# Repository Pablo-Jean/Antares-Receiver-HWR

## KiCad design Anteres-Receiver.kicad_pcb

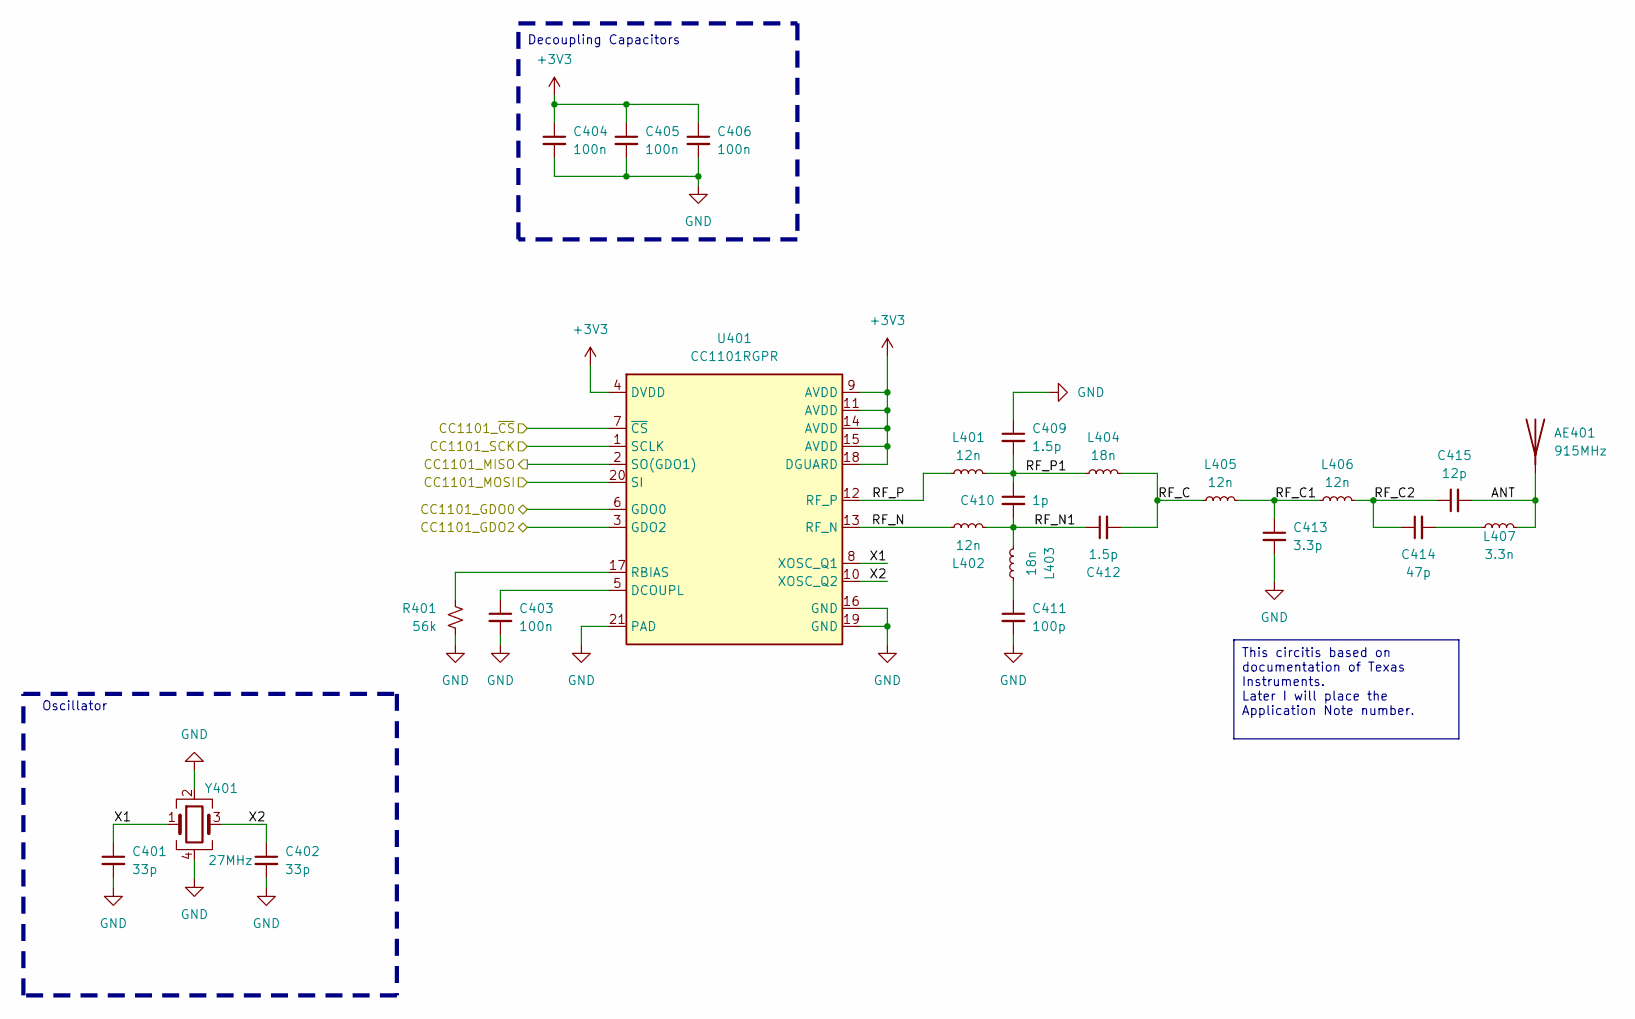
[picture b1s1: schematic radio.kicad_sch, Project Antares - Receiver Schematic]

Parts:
AE401: 915MHz; Texas_SWRA416_868MHz_915MHz
C401, C402: 33p; C_0603_1608Metric; LCSC C107047
C403, C404, C405, C406: 100n; C_0603_1608Metric; LCSC C14663
C409, C412: 1.5p; C_0603_1608Metric; LCSC C519100
C410: 1p; C_0603_1608Metric; LCSC C115062
C411: 100p; C_0603_1608Metric; LCSC C14665
C413: 3.3p; C_0603_1608Metric; LCSC C282249
C414: 47p; C_0603_1608Metric; LCSC C105622
C415: 12p; C_0603_1608Metric; LCSC C107034
L401, L402, L405, L406: 12n; L_0603_1608Metric; LCSC C75656
L403, L404: 18n; L_0603_1608Metric; LCSC C90206
L407: 3.3n; L_0603_1608Metric; LCSC C1029
R401: 56k; R_0603_1608Metric; LCSC C23206
U401: CC1101RGPR; QFN-20-1EP_4x4mm_P0.5mm_EP2.5x2.5mm_ThermalVias; LCSC C29953
Y401: 27MHz; Crystal_SMD_3225-4Pin_3.2x2.5mm; LCSC C9008

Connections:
+3V3: C404.1, C405.1, C406.1, U401.4 (DVDD), U401.9 (AVDD), U401.11 (AVDD), U401.14 (AVDD), U401.15 (AVDD), U401.18 (DGUARD); also elsewhere on the board
/MCU/CC1101_GDO0: U401.6 (GDO0); also elsewhere on the board
/MCU/CC1101_GDO2: U401.3 (GDO2); also elsewhere on the board
/MCU/CC1101_MISO: U401.2 (SO(GDO1)); also elsewhere on the board
/MCU/CC1101_MOSI: U401.20 (SI); also elsewhere on the board
/MCU/CC1101_SCK: U401.1 (SCLK); also elsewhere on the board
/MCU/CC1101_~CS: U401.7 (~CS); also elsewhere on the board
/Radio 915MHz/ANT: AE401.1 (A), C415.2, L407.2
/Radio 915MHz/RF_C: C412.2, L404.2, L405.1
/Radio 915MHz/RF_C1: C413.1, L405.2, L406.1
/Radio 915MHz/RF_C2: C414.1, C415.1, L406.2
/Radio 915MHz/RF_N: L402.1, U401.13 (RF_N)
/Radio 915MHz/RF_N1: C410.2, C412.1, L402.2, L403.2
/Radio 915MHz/RF_P: L401.1, U401.12 (RF_P)
/Radio 915MHz/RF_P1: C409.2, C410.1, L401.2, L404.1
/Radio 915MHz/X1: C401.1, U401.8 (XOSC_Q1), Y401.1
/Radio 915MHz/X2: C402.1, U401.10 (XOSC_Q2), Y401.3
GND: C401.2, C402.2, C403.2, C404.2, C405.2, C406.2, C409.1, C411.2, C413.2, R401.2, U401.16 (GND), U401.19 (GND), U401.21 (PAD), Y401.2, Y401.4; also elsewhere on the board
unnamed: C411.1, L403.1
unnamed: C414.2, L407.1
unnamed: C403.1, U401.5 (DCOUPL)
unnamed: R401.1, U401.17 (RBIAS)

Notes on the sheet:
This circitis based on documentation of Texas Instruments. Later I will place the Application Note number.
Oscillator
Decoupling Capacitors

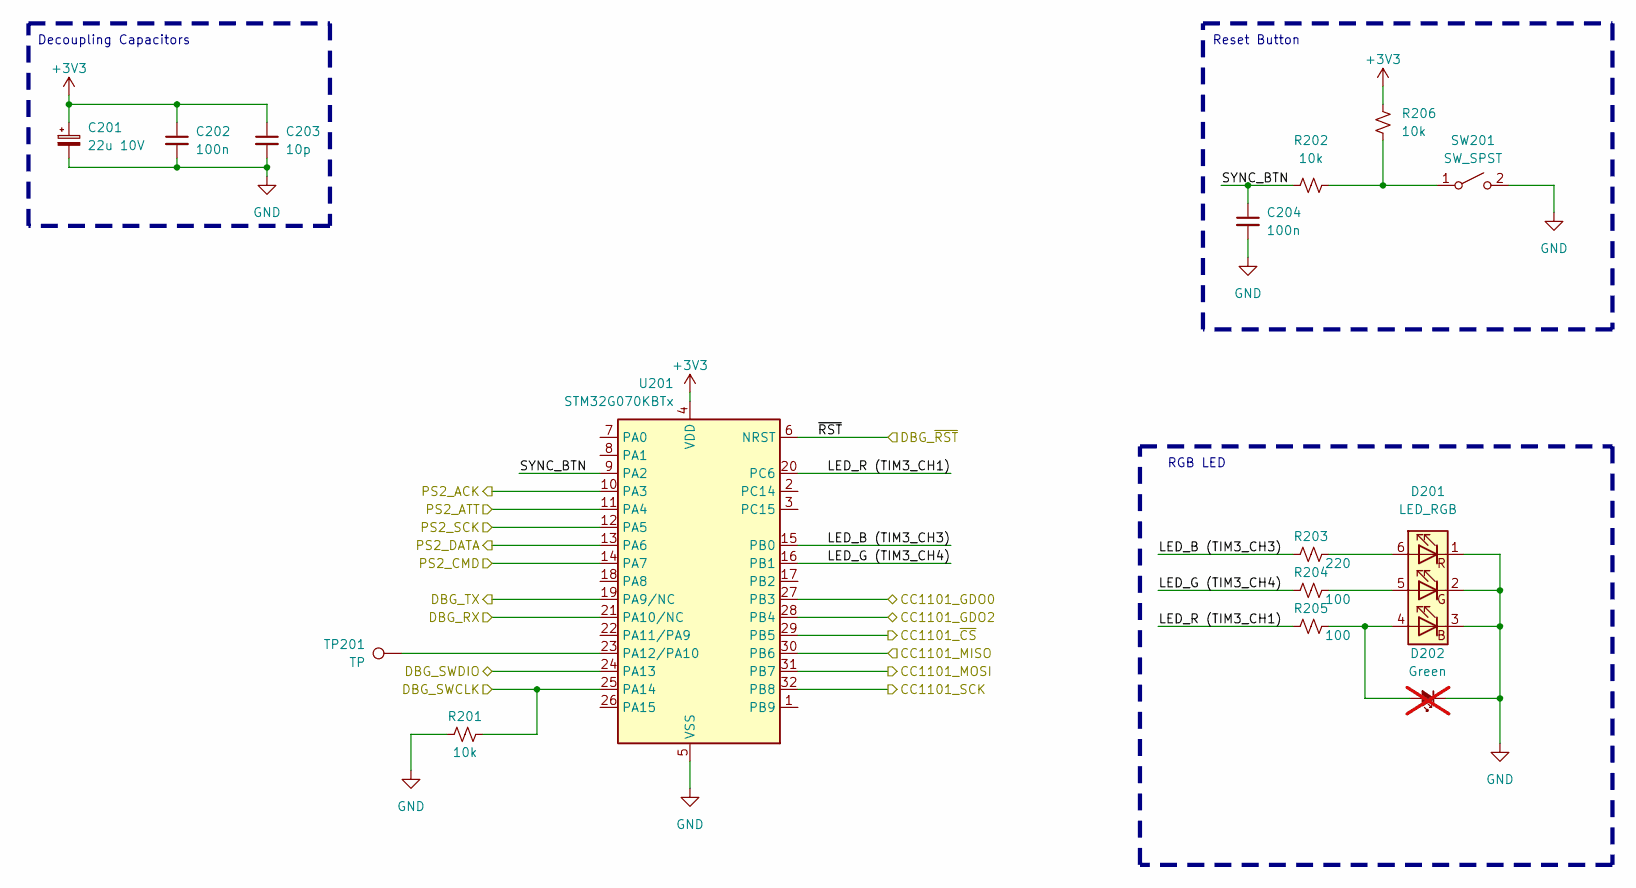
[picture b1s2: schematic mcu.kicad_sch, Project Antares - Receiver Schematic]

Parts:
C201: 22u 10V; CP_EIA-3216-12_Kemet-S; LCSC C129272
C202, C204: 100n; C_0603_1608Metric; LCSC C14663
C203: 10p; C_0603_1608Metric; LCSC C106245
D201: LED_RGB; LED_RGB_5050-6; LCSC C913089
D202: Green; LED_0603_1608Metric; LCSC C965804; not fitted
R201, R202, R206: 10k; R_0603_1608Metric; LCSC C25804
R203: 220; R_0603_1608Metric; LCSC C23345
R204, R205: 100; R_0603_1608Metric; LCSC C22775
SW201: SW_SPST; SW_Push_1P1T_NO_6x6mm_H9.5mm; LCSC C3038675
TP201: TP; TestPoint_Pad_D2.0mm
U201: STM32G070KBTx; LQFP-32_7x7mm_P0.8mm; LCSC C529339

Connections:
+3V3: C201.1, C202.1, C203.1, R206.1, U201.4 (VDD); also elsewhere on the board
/Debugging/DBG_RX: U201.21 (PA10/NC); also elsewhere on the board
/Debugging/DBG_SWCLK: R201.2, U201.25 (PA14); also elsewhere on the board
/Debugging/DBG_SWDIO: U201.24 (PA13); also elsewhere on the board
/Debugging/DBG_TX: U201.19 (PA9/NC); also elsewhere on the board
/MCU/CC1101_GDO0: U201.27 (PB3); also elsewhere on the board
/MCU/CC1101_GDO2: U201.28 (PB4); also elsewhere on the board
/MCU/CC1101_MISO: U201.30 (PB6); also elsewhere on the board
/MCU/CC1101_MOSI: U201.31 (PB7); also elsewhere on the board
/MCU/CC1101_SCK: U201.32 (PB8); also elsewhere on the board
/MCU/CC1101_~CS: U201.29 (PB5); also elsewhere on the board
/MCU/LED_B (TIM3_CH3): R203.1, U201.15 (PB0)
/MCU/LED_G (TIM3_CH4): R204.1, U201.16 (PB1)
/MCU/LED_R (TIM3_CH1): R205.1, U201.20 (PC6)
/MCU/PS2_ACK: U201.10 (PA3); also elsewhere on the board
/MCU/PS2_ATT: U201.11 (PA4); also elsewhere on the board
/MCU/PS2_CMD: U201.14 (PA7); also elsewhere on the board
/MCU/PS2_DATA: U201.13 (PA6); also elsewhere on the board
/MCU/PS2_SCK: U201.12 (PA5); also elsewhere on the board
/MCU/SYNC_BTN: C204.1, R202.1, U201.9 (PA2)
/MCU/~RST: U201.6 (NRST); also elsewhere on the board
GND: C201.2, C202.2, C203.2, C204.2, D201.1 (RK), D201.2 (GK), D201.3 (BK), D202.1 (K), R201.1, SW201.2 (B), U201.5 (VSS); also elsewhere on the board
unnamed: D201.4 (BA), D202.2 (A), R205.2
unnamed: D201.5 (GA), R204.2
unnamed: D201.6 (RA), R203.2
unnamed: R202.2, R206.2, SW201.1 (A)
unnamed: TP201.1, U201.23 (PA12/PA10)

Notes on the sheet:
Reset Button
Decoupling Capacitors
RGB LED

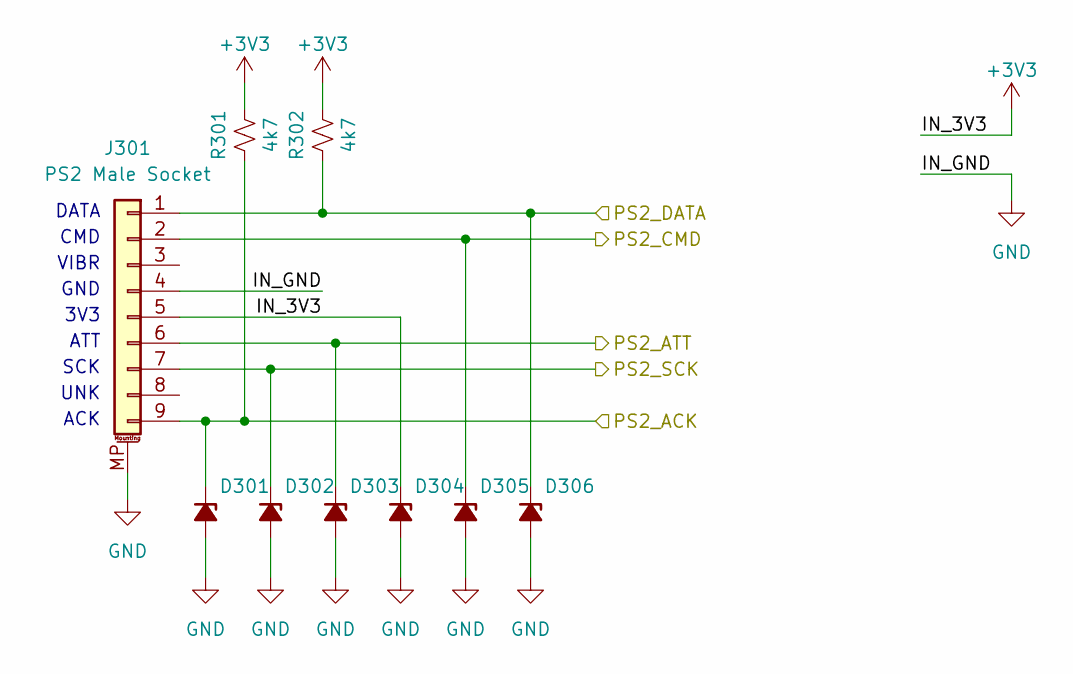
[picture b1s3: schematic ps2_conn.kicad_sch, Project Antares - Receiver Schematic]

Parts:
D301, D302, D303, D304, D305, D306: 3V3; D_SOD-123; LCSC C173413
J301: PS2 Male Socket; dualshock-9pin-P4.00mm
R301, R302: 4k7; R_0603_1608Metric; LCSC C23162

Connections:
+3V3: D304.1 (K), J301.5, R301.2, R302.2; also elsewhere on the board
/MCU/PS2_ACK: D301.1 (K), J301.9, R301.1; also elsewhere on the board
/MCU/PS2_ATT: D303.1 (K), J301.6; also elsewhere on the board
/MCU/PS2_CMD: D305.1 (K), J301.2; also elsewhere on the board
/MCU/PS2_DATA: D306.1 (K), J301.1, R302.1; also elsewhere on the board
/MCU/PS2_SCK: D302.1 (K), J301.7; also elsewhere on the board
GND: D301.2 (A), D302.2 (A), D303.2 (A), D304.2 (A), D305.2 (A), D306.2 (A), J301.4, J301.MP (MountPin); also elsewhere on the board

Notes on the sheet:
DATA
ACK
SCK
UNK
GND
CMD
VIBR
ATT
3V3

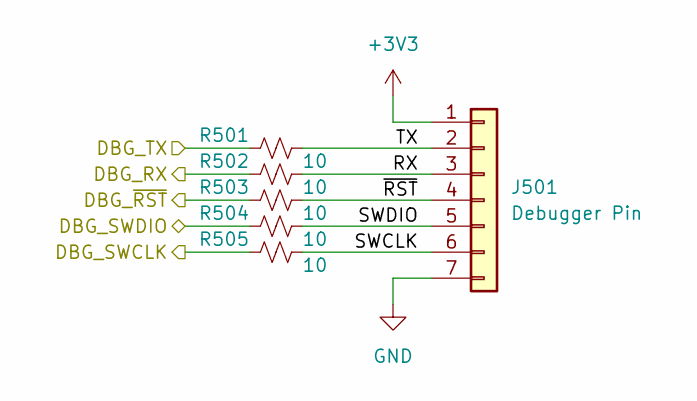
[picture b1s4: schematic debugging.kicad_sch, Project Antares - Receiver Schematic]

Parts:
J501: Debugger Pin; PinHeader_1x07_P2.54mm_Vertical
R501, R502, R503, R504, R505: 10; R_0603_1608Metric; LCSC C22859

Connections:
+3V3: J501.1; also elsewhere on the board
/Debugging/DBG_RX: R502.1; also elsewhere on the board
/Debugging/DBG_SWCLK: R505.1; also elsewhere on the board
/Debugging/DBG_SWDIO: R504.1; also elsewhere on the board
/Debugging/DBG_TX: R501.1; also elsewhere on the board
/Debugging/RX: J501.3, R502.2
/Debugging/SWCLK: J501.6, R505.2
/Debugging/SWDIO: J501.5, R504.2
/Debugging/TX: J501.2, R501.2
/Debugging/~RST: J501.4, R503.2
/MCU/~RST: R503.1; also elsewhere on the board
GND: J501.7; also elsewhere on the board

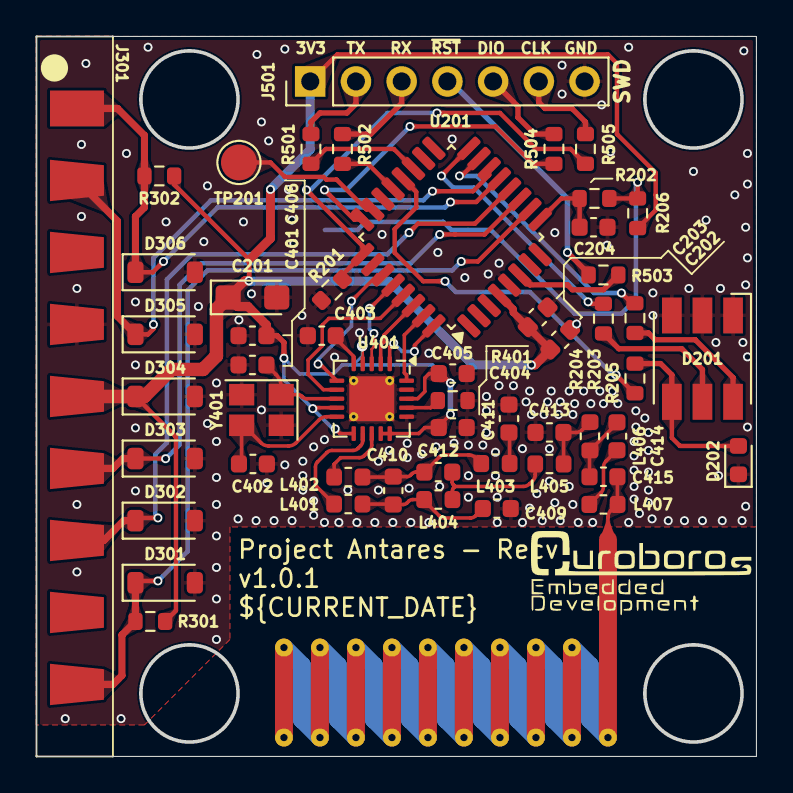
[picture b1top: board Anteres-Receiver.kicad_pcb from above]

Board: 2 copper layers, 39.9 x 39.9 mm, 54 parts (1 on the bottom side), 46 nets.

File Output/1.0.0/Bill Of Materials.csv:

"Reference","Value","Footprint","Qty","DNP","PN","LCSC"
"AE401","915MHz","RF_Antenna:Texas_SWRA416_868MHz_915MHz","1","","",""
"C201","22u 10V","Capacitor_Tantalum_SMD:CP_EIA-3216-12_Kemet-S","1","","CA45-A-10V-22uF-K","C129272"
"C202,C204,C403,C404,C405,C406","100n","Capacitor_SMD:C_0603_1608Metric","6","","CC0603KRX7R9BB104","C14663"
"C203","10p","Capacitor_SMD:C_0603_1608Metric","1","","CC0603JRNPO9BN100","C106245"
"C401,C402","33p","Capacitor_SMD:C_0603_1608Metric","2","","CC0603JRNPO9BN330","C107047"
"C409,C412","1.5p","Capacitor_SMD:C_0603_1608Metric","2","","CC0603BRNPO9BN1R5","C519100"
"C410","1p","Capacitor_SMD:C_0603_1608Metric","1","","CC0603BRNPO9BN1R0","C115062"
"C411","100p","Capacitor_SMD:C_0603_1608Metric","1","","CC0603JRNPO9BN101","C14665"
"C413","3.3p","Capacitor_SMD:C_0603_1608Metric","1","","CC0603CRNPO9BN3R3","C282249"
"C414","47p","Capacitor_SMD:C_0603_1608Metric","1","","CC0603JRNPO9BN470","C105622"
"C415","12p","Capacitor_SMD:C_0603_1608Metric","1","","CC0603JRNPO9BN120","C107034"
"D201","LED_RGB","LED_SMD:LED_RGB_5050-6","1","","LTST-G563EGBW","C913089"
"D202","Green","LED_SMD:LED_0603_1608Metric","1","DNP","XL-1608UGC-04","C965804"
"D301,D302,D303,D304,D305,D306","3V3","Diode_SMD:D_SOD-123","6","","BZT52C3V3","C173413"
"J301","PS2 Male Socket","PS2_Conn:dualshock-9pin-P4.00mm","1","","",""
"J501","Debugger Pin","Connector_PinHeader_2.54mm:PinHeader_1x07_P2.54mm_Vertical","1","","",""
"L401,L402,L405,L406","12n","Inductor_SMD:L_0603_1608Metric","4","","VHF160808H12NJT","C75656"
"L403,L404","18n","Inductor_SMD:L_0603_1608Metric","2","","VHF160808H18NJT","C90206"
"L407","3.3n","Inductor_SMD:L_0603_1608Metric","1","","VHF160808H3N3ST","C1029"
"R201,R202,R206","10k","Resistor_SMD:R_0603_1608Metric","3","","FRC0603J103TS","C2930027"
"R203","220","Resistor_SMD:R_0603_1608Metric","1","","FRC0603J221 TS","C2907127"
"R204,R205","100","Resistor_SMD:R_0603_1608Metric","2","","0603WAJ0101T5E","C25201"
"R301,R302","4k7","Resistor_SMD:R_0603_1608Metric","2","","0603WAJ0472T5E","C25999"
"R401","56k","Resistor_SMD:R_0603_1608Metric","1","","RC0603FR-0756KL","C114630"
"R501,R502,R503,R504,R505","10","Resistor_SMD:R_0603_1608Metric","5","","0603WAJ0100T5E","C25202"
"SW201","SW_SPST","Button_Switch_SMD:SW_Push_1P1T_NO_6x6mm_H9.5mm","1","","KH-6X6X9.5H-SMT","C3038675"
"TP201","TP","TestPoint:TestPoint_Pad_D2.0mm","1","","",""
"U201","STM32G070KBTx","Package_QFP:LQFP-32_7x7mm_P0.8mm","1","","STM32G070KBT6","C529339"
"U401","CC1101RGPR","Package_DFN_QFN:QFN-20-1EP_4x4mm_P0.5mm_EP2.5x2.5mm_ThermalVias","1","","CC1101RGPR","C29953"
"Y401","27MHz","Crystal:Crystal_SMD_3225-4Pin_3.2x2.5mm","1","","X322527MSB4SI","C9008"

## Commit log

2024-08-23 :tada: first commit
2024-08-23 :memo: updated schemati and pcb information
2024-08-23 :package: created v1.0.0 production files
2024-08-23 updated resistor values
2024-08-24 :minidisc: fixed dvdd of cc1101 pin unconnected
2024-09-04 :memo: added schematic model sheet
